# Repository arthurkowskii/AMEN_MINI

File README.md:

# AMEN_MINI

AMEN_MINI is a standalone sample player for sound design: assign WAV files from the native microSD card to 20 pads and play up to four sources simultaneously.

## The PCB

### Blueprints (KiCad)

### The assembled board

The board is a 2-layer, 1.6 mm PCB hosting a socketed Teensy 4.1, with the PJRC Audio Adapter (SGTL5000) plugged into J3/J4. Ordering and assembly details live in `hardware/BOM_AMEN_MINI.csv`.

## Hardware

- **Teensy 4.1** (Cortex-M7, 600 MHz) — control processor, native microSD and USB; no PSRAM required;
- **PJRC Audio Adapter SGTL5000** — headphone + line output;
- 21 MX-compatible switches: 20 source pads + Shift;
- 7 EC11 push encoders;
- SSD1306 I²C OLED, 0.91″, 128 × 32;
- WAV PCM 16-bit / 44.1 kHz, mono or stereo, streamed from SD through fixed RAM buffers.

## Firmware

- `firmware/firmware.ino` — Teensy entrypoint;
- `firmware/src/engine/` — portable C++17 WAV parser and four-voice streaming mixer;
- `firmware/src/teensy/` — SD, I2S/SGTL5000, controls and OLED integration;
- `firmware/test_native/` — native verification and Windows listening harness;
- `build_firmware.ps1` — Teensy build; `start_firmware.ps1` — PC listening harness.

Shift + pad opens assignment. Turn E1 to browse; click E1 to enter a folder or assign a WAV. Press Shift again to cancel. E7 controls headphone volume, displayed on the OLED and reset to mute at startup. Pads play one-shots; assignments are volatile. Crop, effects and MIDI are outside this initial firmware.

## Status

- **Hardware**: PCB fabricated and photographed (above). The Teensy 4.1 + Audio Adapter build is the current target.
- **Firmware**: active development on `dev`. The MIDI firmware (`firmware_midi/`, restored, boots CHROMATIC + NONE) is the currently flashed instrument firmware; native tests and Teensy build pass. The minimal SD sample player (`firmware/`) is blocked on hardware: the SGTL5000 never acknowledges (retried at 100/50/10 kHz on 0x0A/0x2A), consecutive bus scans minutes apart report different phantom addresses with only 0x3C stable, and OLED writes have started failing too. The fault is electrical (shield seating/power or shared I2C wiring), not fixable in software.

## License

The repository is licensed under **CC BY-NC 4.0** — see [LICENSE](LICENSE) for the full legal text.

In plain words:

- **Anyone can use, build, modify, and share AMEN_MINI** — for personal or any **non-commercial** use.
- **Commercial use is not allowed** (no selling units, no commercial productions) without prior written permission from the author.
- **Credit**: if you publish content *made with* AMEN_MINI on the internet (music, video, images), credit **Arthur Kowskii Croquebois** (kowskii.com). For personal or offline use, no credit is required.

Made by [Arthur Kowskii Croquebois](https://kowskii.com) — sound designer & game developer.

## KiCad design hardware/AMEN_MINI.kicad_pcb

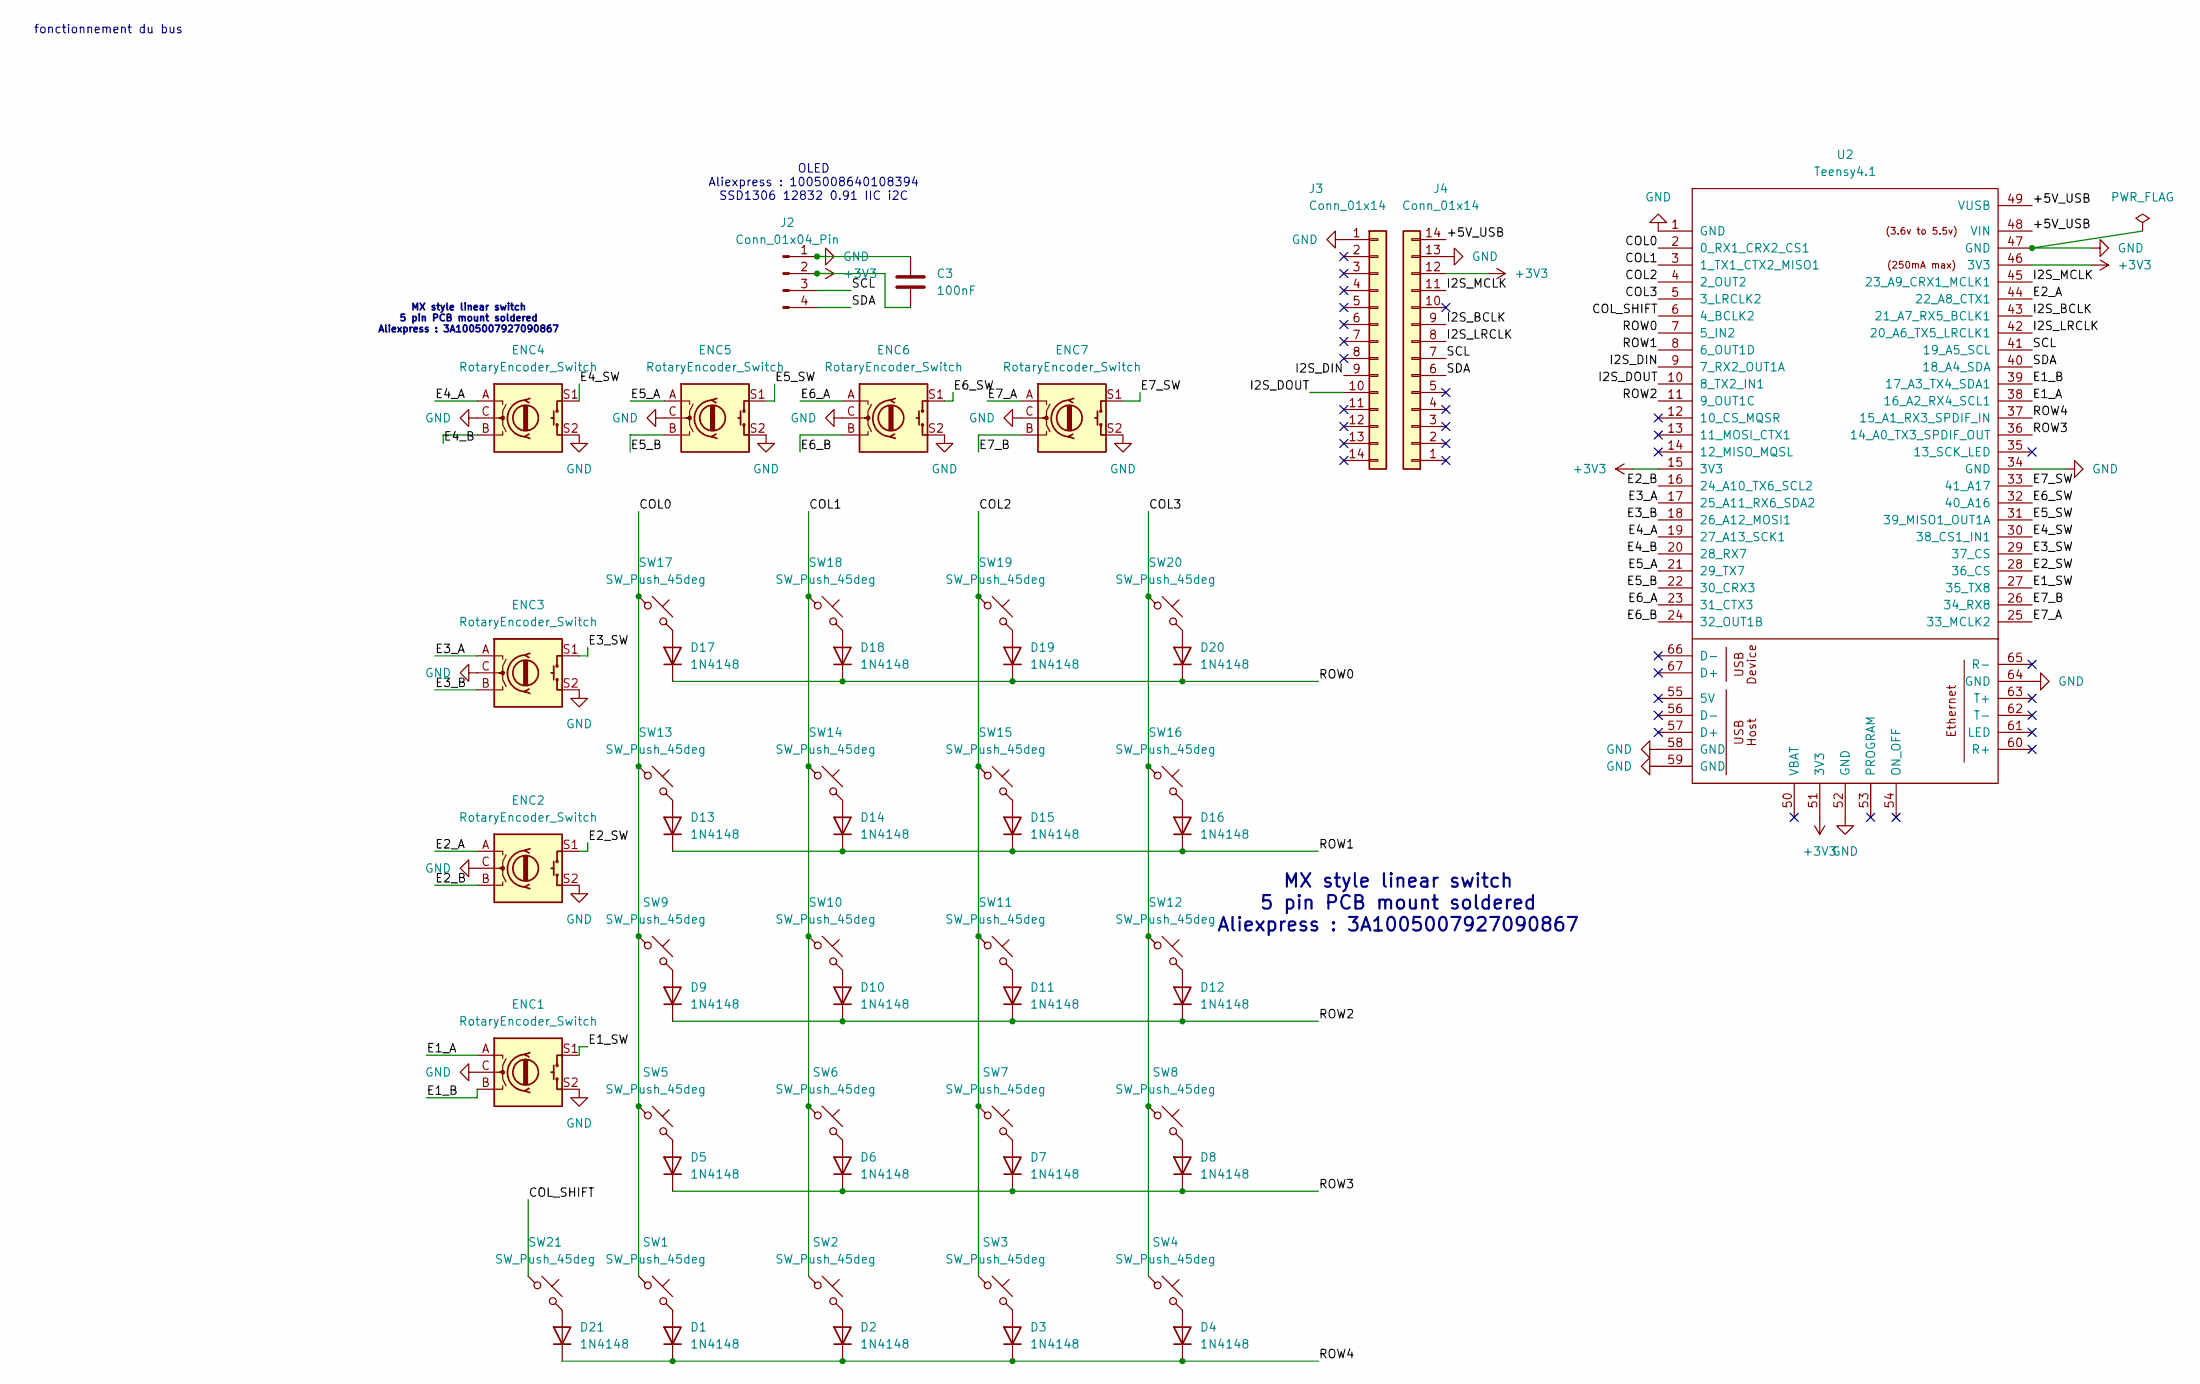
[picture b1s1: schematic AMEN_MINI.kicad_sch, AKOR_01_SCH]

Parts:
C3: 100nF; C_Disc_D5.0mm_W2.5mm_P5.00mm
D1, D2, D3, D4, D5, D6, D7, D8, D9, D10, D11, D12, D13, D14, D15, D16, D17, D18, D19, D20, D21: 1N4148; D_DO-35_SOD27_P10.16mm_Horizontal
ENC1, ENC2, ENC3, ENC4, ENC5, ENC6, ENC7: RotaryEncoder_Switch; RotaryEncoder_Alps_EC11E-Switch_Vertical_H20mm
J2: Conn_01x04_Pin; ER_OLEDM0.91_1x-I2C
J3, J4: Conn_01x14; PinHeader_1x14_P2.54mm_Vertical
SW1, SW2, SW3, SW4, SW5, SW6, SW7, SW8, SW9, SW10, SW11, SW12, SW13, SW14, SW15, SW16, SW17, SW18, SW19, SW20, SW21: SW_Push_45deg; SW_Cherry_MX_1.00u_PCB
U2: Teensy4.1; Teensy41

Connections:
+3V3: C3.2, J2.2, J4.12, U2.15 (3V3), U2.46 (3V3), U2.51 (3V3)
/+5V_USB: J4.14, U2.48 (VIN), U2.49 (VUSB)
/COL0: SW1.1, SW5.1, SW9.1, SW13.1, SW17.1, U2.2 (0_RX1_CRX2_CS1)
/COL1: SW2.1, SW6.1, SW10.1, SW14.1, SW18.1, U2.3 (1_TX1_CTX2_MISO1)
/COL2: SW3.1, SW7.1, SW11.1, SW15.1, SW19.1, U2.4 (2_OUT2)
/COL3: SW4.1, SW8.1, SW12.1, SW16.1, SW20.1, U2.5 (3_LRCLK2)
/COL_SHIFT: SW21.1, U2.6 (4_BCLK2)
/E1_A: ENC1.A, U2.38 (16_A2_RX4_SCL1)
/E1_B: ENC1.B, U2.39 (17_A3_TX4_SDA1)
/E1_SW: ENC1.S1, U2.27 (35_TX8)
/E2_A: ENC2.A, U2.44 (22_A8_CTX1)
/E2_B: ENC2.B, U2.16 (24_A10_TX6_SCL2)
/E2_SW: ENC2.S1, U2.28 (36_CS)
/E3_A: ENC3.A, U2.17 (25_A11_RX6_SDA2)
/E3_B: ENC3.B, U2.18 (26_A12_MOSI1)
/E3_SW: ENC3.S1, U2.29 (37_CS)
/E4_A: ENC4.A, U2.19 (27_A13_SCK1)
/E4_B: ENC4.B, U2.20 (28_RX7)
/E4_SW: ENC4.S1, U2.30 (38_CS1_IN1)
/E5_A: ENC5.A, U2.21 (29_TX7)
/E5_B: ENC5.B, U2.22 (30_CRX3)
/E5_SW: ENC5.S1, U2.31 (39_MISO1_OUT1A)
/E6_A: ENC6.A, U2.23 (31_CTX3)
/E6_B: ENC6.B, U2.24 (32_OUT1B)
/E6_SW: ENC6.S1, U2.32 (40_A16)
/E7_A: ENC7.A, U2.25 (33_MCLK2)
/E7_B: ENC7.B, U2.26 (34_RX8)
/E7_SW: ENC7.S1, U2.33 (41_A17)
/I2S_BCLK: J4.9, U2.43 (21_A7_RX5_BCLK1)
/I2S_DIN: J3.9, U2.9 (7_RX2_OUT1A)
/I2S_DOUT: J3.10, U2.10 (8_TX2_IN1)
/I2S_LRCLK: J4.8, U2.42 (20_A6_TX5_LRCLK1)
/I2S_MCLK: J4.11, U2.45 (23_A9_CRX1_MCLK1)
/ROW0: D17.1 (K), D18.1 (K), D19.1 (K), D20.1 (K), U2.7 (5_IN2)
/ROW1: D13.1 (K), D14.1 (K), D15.1 (K), D16.1 (K), U2.8 (6_OUT1D)
/ROW2: D9.1 (K), D10.1 (K), D11.1 (K), D12.1 (K), U2.11 (9_OUT1C)
/ROW3: D5.1 (K), D6.1 (K), D7.1 (K), D8.1 (K), U2.36 (14_A0_TX3_SPDIF_OUT)
/ROW4: D1.1 (K), D2.1 (K), D3.1 (K), D4.1 (K), D21.1 (K), U2.37 (15_A1_RX3_SPDIF_IN)
/SCL: J2.3, J4.7, U2.41 (19_A5_SCL)
/SDA: J2.4, J4.6, U2.40 (18_A4_SDA)
GND: C3.1, ENC1.C, ENC1.S2, ENC2.C, ENC2.S2, ENC3.C, ENC3.S2, ENC4.C, ENC4.S2, ENC5.C, ENC5.S2, ENC6.C, ENC6.S2, ENC7.C, ENC7.S2, J2.1, J3.1, J4.13, U2.1 (GND), U2.34 (GND), U2.47 (GND), U2.52 (GND), U2.58 (GND), U2.59 (GND), U2.64 (GND)
unnamed: D1.2 (A), SW1.2
unnamed: D2.2 (A), SW2.2
unnamed: D3.2 (A), SW3.2
unnamed: D4.2 (A), SW4.2
unnamed: D5.2 (A), SW5.2
unnamed: D6.2 (A), SW6.2
unnamed: D7.2 (A), SW7.2
unnamed: D8.2 (A), SW8.2
unnamed: D9.2 (A), SW9.2
unnamed: D10.2 (A), SW10.2
unnamed: D11.2 (A), SW11.2
unnamed: D12.2 (A), SW12.2
unnamed: D13.2 (A), SW13.2
unnamed: D14.2 (A), SW14.2
unnamed: D15.2 (A), SW15.2
unnamed: D16.2 (A), SW16.2
unnamed: D17.2 (A), SW17.2
unnamed: D18.2 (A), SW18.2
unnamed: D19.2 (A), SW19.2
unnamed: D20.2 (A), SW20.2
unnamed: D21.2 (A), SW21.2

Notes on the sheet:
MX style linear switch 5 pin PCB mount soldered Aliexpress : 3A1005007927090867
fonctionnement du bus
OLED Aliexpress : 1005008640108394 SSD1306 12832 0.91 IIC i2C

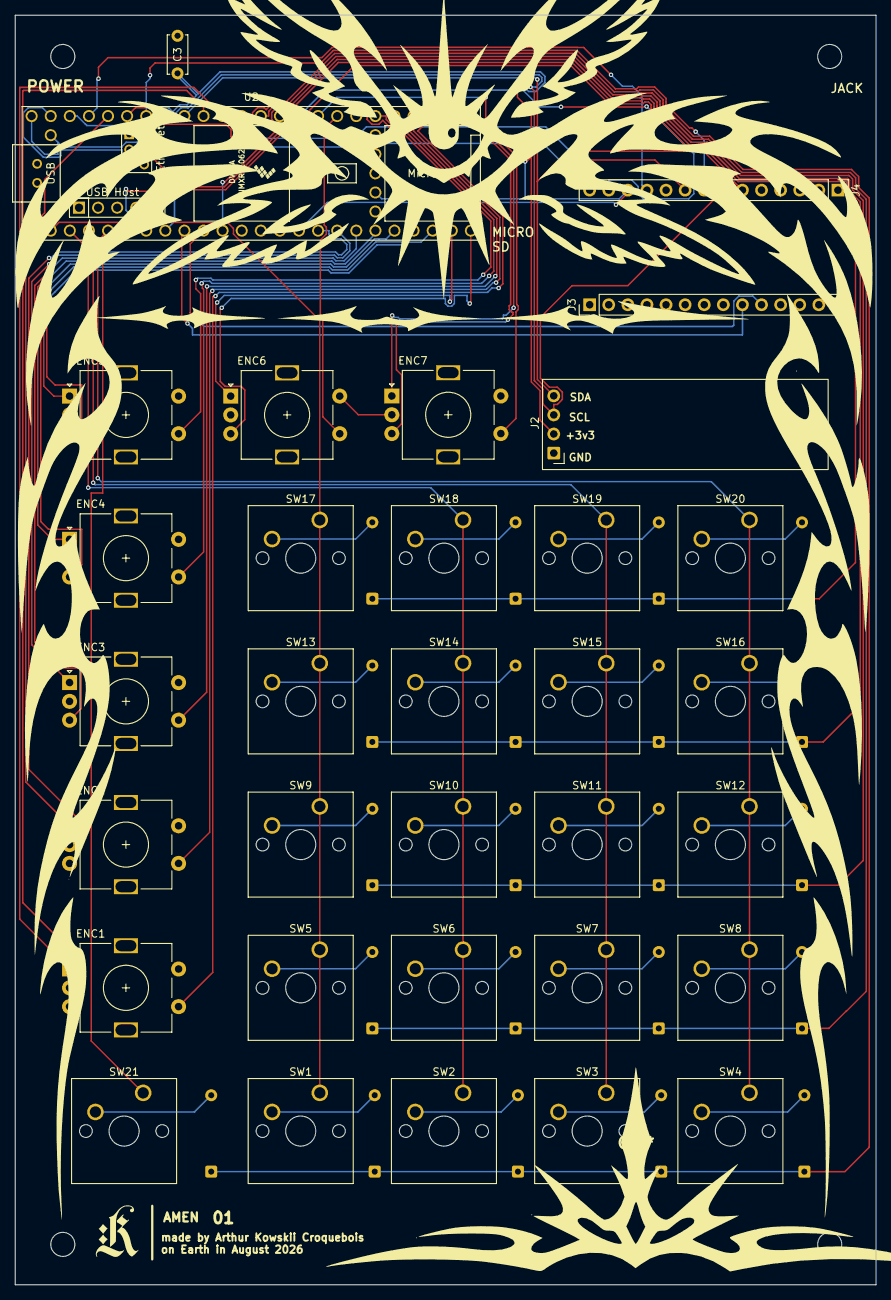
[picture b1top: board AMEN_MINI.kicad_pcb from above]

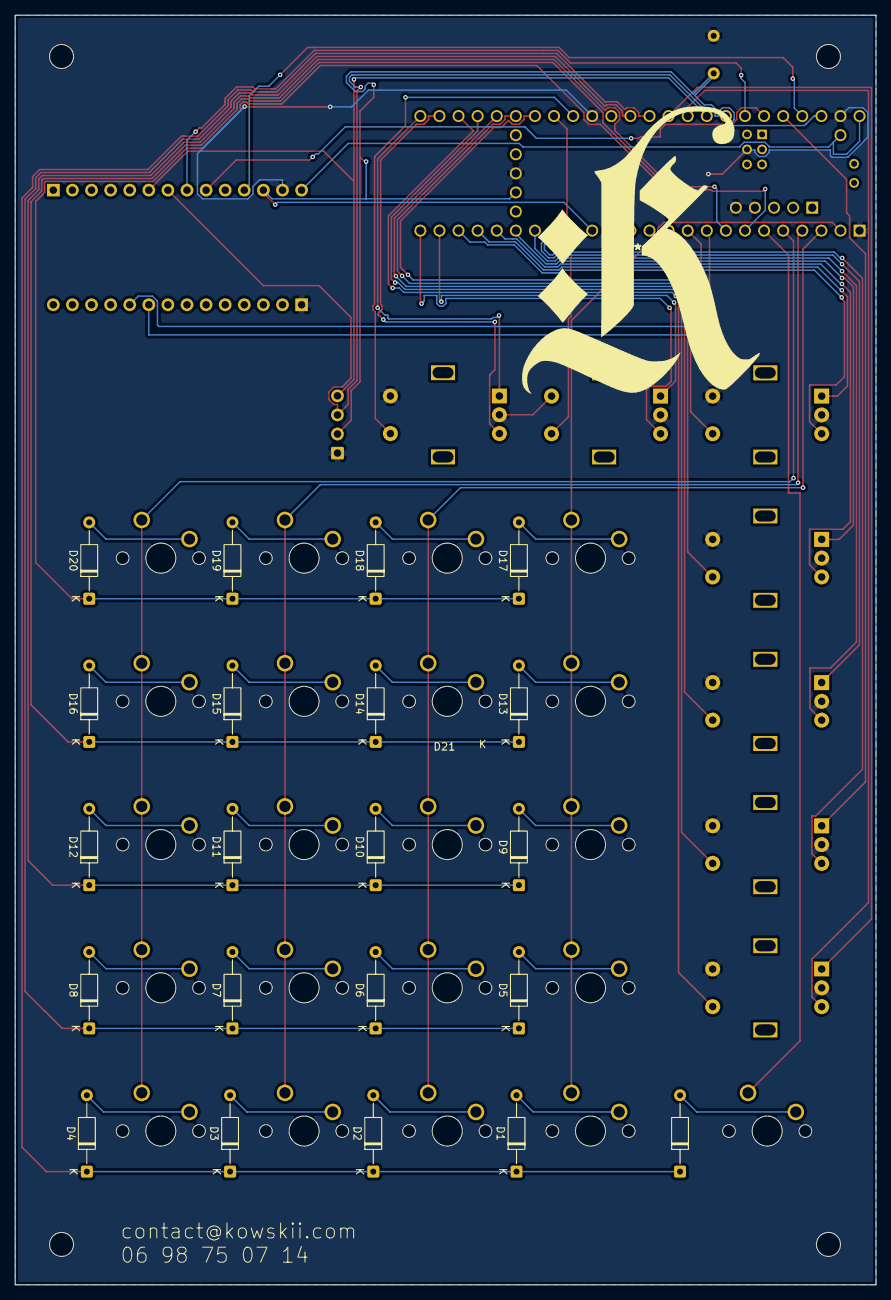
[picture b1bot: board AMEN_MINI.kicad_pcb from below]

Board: 2 copper layers, 114.5 x 168.9 mm, 54 parts (21 on the bottom side), 62 nets.
